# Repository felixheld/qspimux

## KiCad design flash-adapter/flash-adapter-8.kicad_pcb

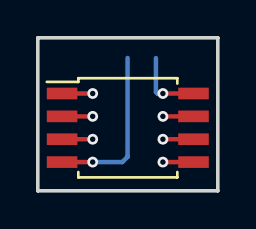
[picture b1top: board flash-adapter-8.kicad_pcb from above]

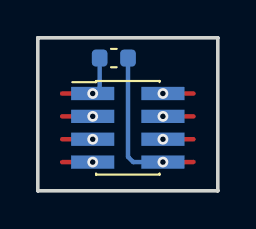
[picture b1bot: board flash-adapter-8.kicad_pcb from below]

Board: 2 copper layers, 10.0 x 8.5 mm, 3 parts (2 on the bottom side), 8 nets.

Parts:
C101: 100n; C_0603_1608Metric
J101: Conn_02x04_Odd_Even; PinHeader_2x04_P1.27mm_Vertical_SMD
U101: W25Q64FVSS; SOIJ-8_5.3x5.3mm_P1.27mm

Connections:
/CLK: J101.5, U101.6
/DQ0: J101.7, U101.5
/DQ1: J101.4, U101.2
/GND: C101.2, J101.8, U101.4
/VCC: C101.1, J101.1, U101.8
/~CS: J101.2, U101.1
/~HOLD: J101.3, U101.7
/~WP: J101.6, U101.3

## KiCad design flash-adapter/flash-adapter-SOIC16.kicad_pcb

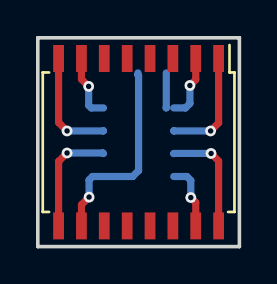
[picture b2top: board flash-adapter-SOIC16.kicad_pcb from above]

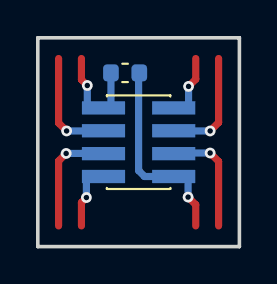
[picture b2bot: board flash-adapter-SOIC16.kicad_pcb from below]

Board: 2 copper layers, 11.2 x 11.6 mm, 3 parts (2 on the bottom side), 8 nets.

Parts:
C101: 100n; C_0603_1608Metric
J101: Conn_02x04_Odd_Even; PinHeader_2x04_P1.27mm_Vertical_SMD
U101: W25Q64FVSF; SOIC-16W_7.5x10.3mm_P1.27mm

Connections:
/CLK: J101.5, U101.16
/DQ0: J101.7, U101.15
/DQ1: J101.4, U101.8
/GND: C101.2, J101.8, U101.10
/VCC: C101.1, J101.1, U101.2
/~CS: J101.2, U101.7
/~HOLD: J101.3, U101.1
/~WP: J101.6, U101.9
